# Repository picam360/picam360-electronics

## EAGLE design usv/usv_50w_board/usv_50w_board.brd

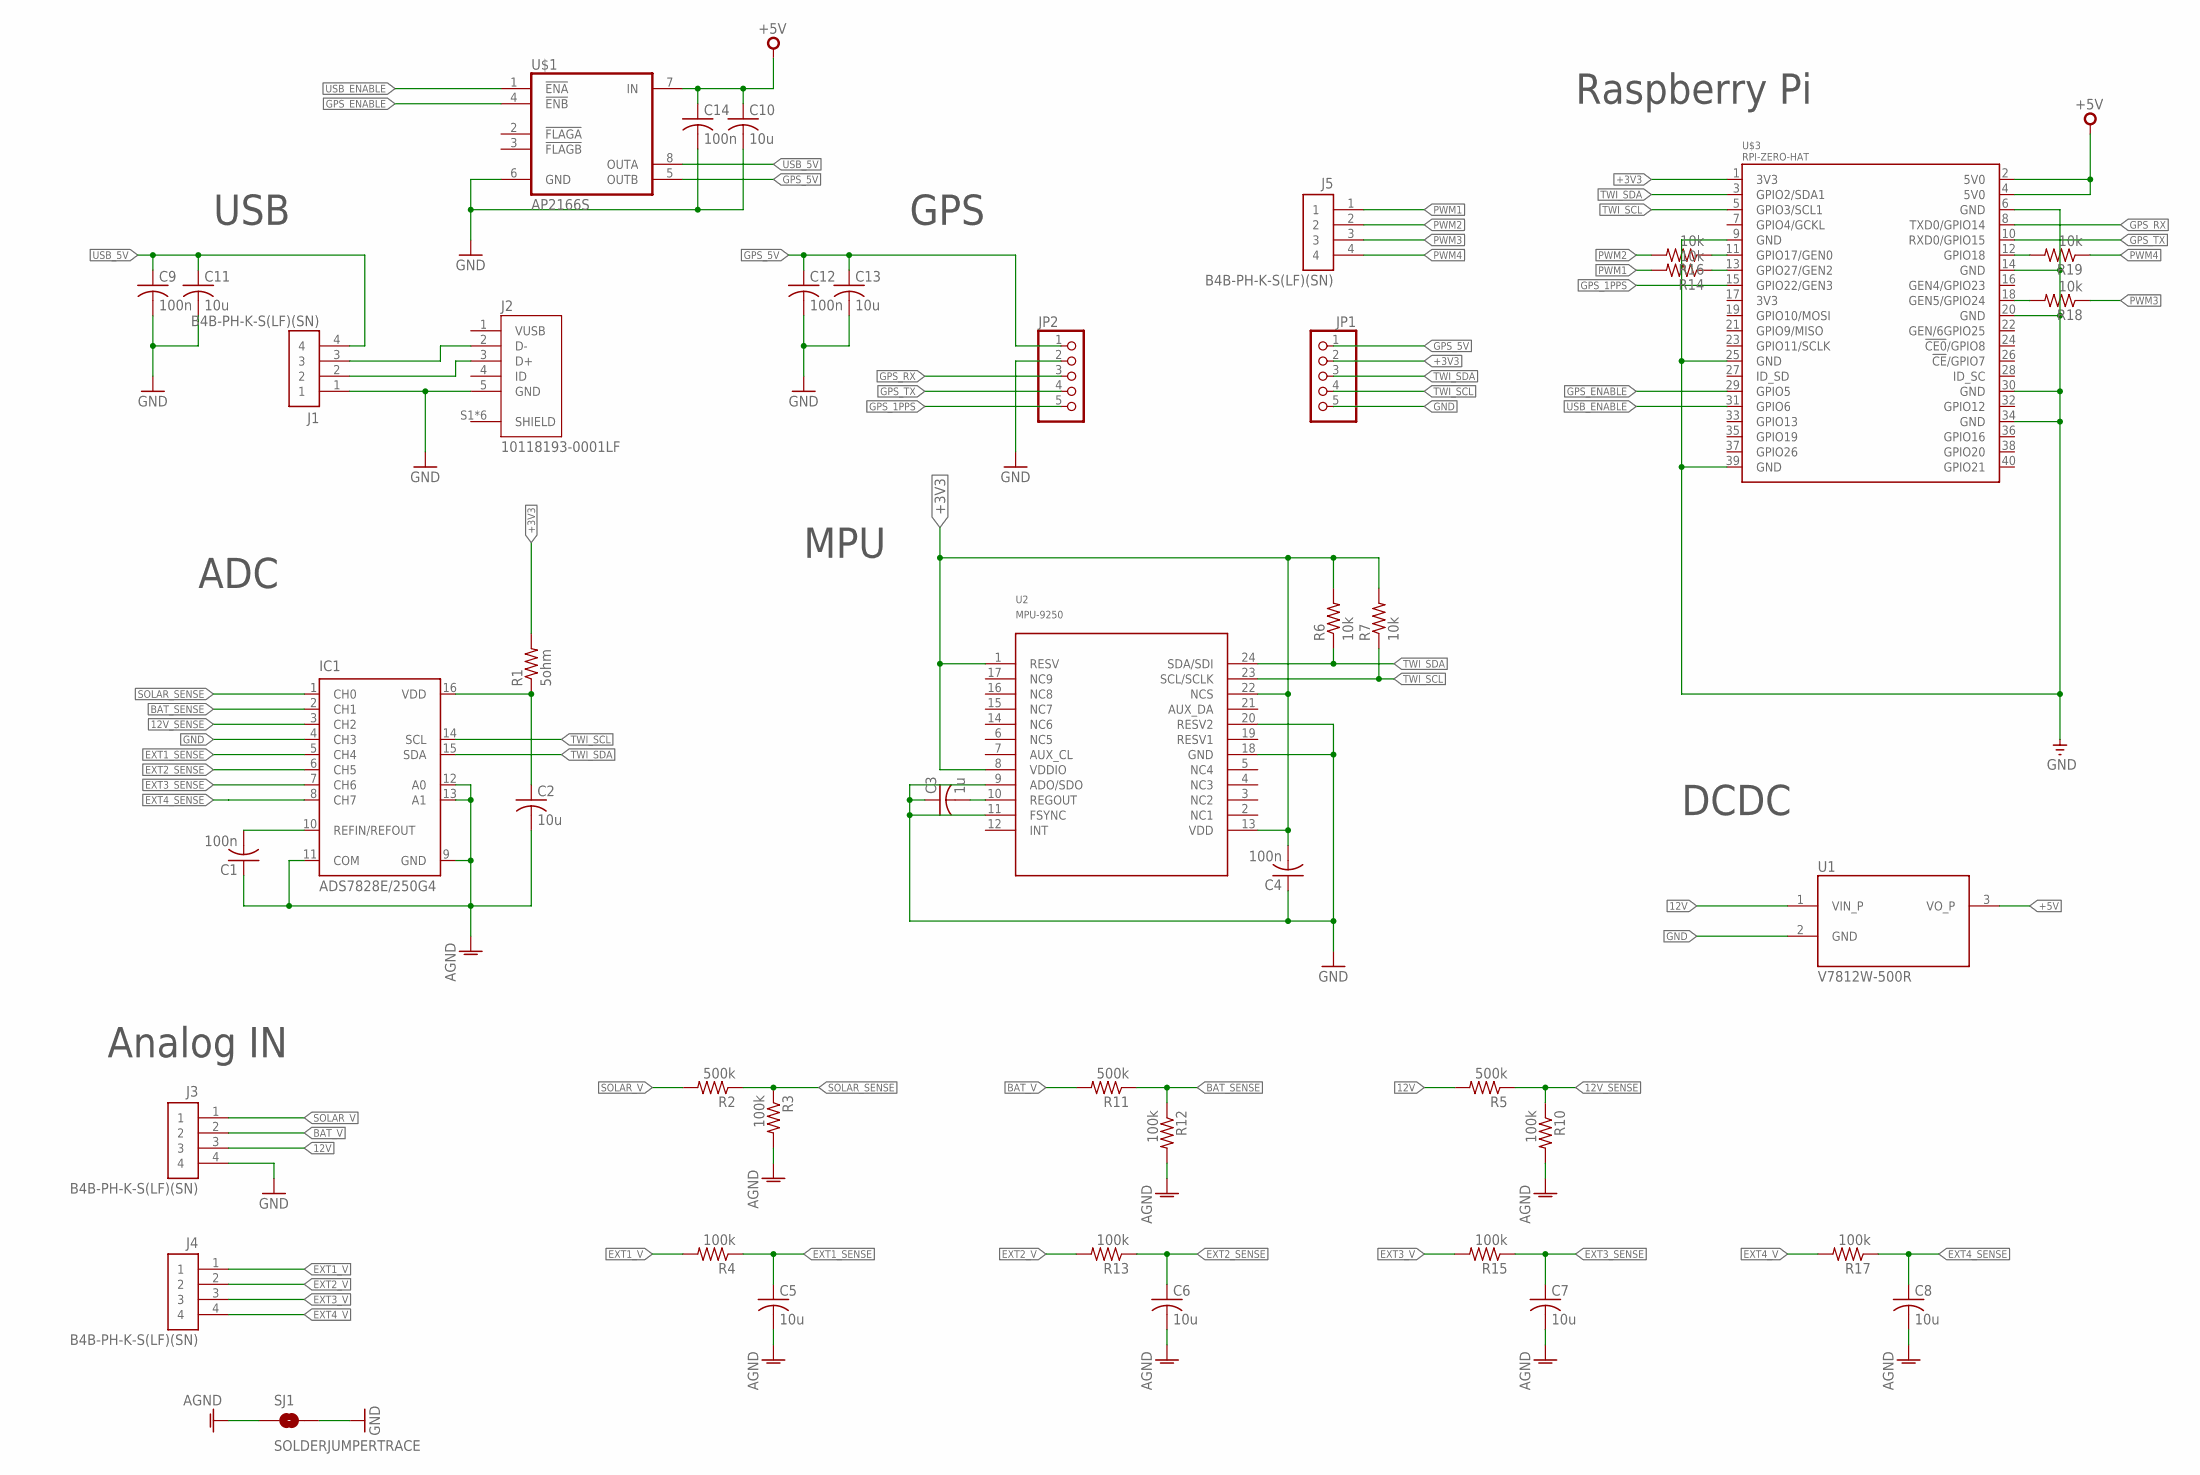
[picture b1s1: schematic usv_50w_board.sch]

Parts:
C1, C4, C9, C12, C14: 100n; C0603
C2, C5, C6, C7, C8, C10, C11, C13: 10u; C0603
C3: 1u; C0603
IC1: ADS7828E/250G4; TSSOP16-PW
J1, J3, J4, J5: B4B-PH-K-S(LF)(SN); JST_B4B-PH-K-S(LF)(SN)
J2: 10118193-0001LF; FCI_10118193-0001LF
JP1, JP2: PINHD-1X5; 1X05
R1: 5ohm; R0603
R2, R5, R11: 500k; R0603
R3, R4, R10, R12, R13, R15, R17: 100k; R0603
R6, R7, R14, R16, R18, R19: 10k; R0603
SJ1: SOLDERJUMPERTRACE; SJ_2S-TRACE
U1: V7812W-500R; CONV_V7812W-500R
U2: MPU-9250; LEAD-QFN24
U$1: AP2166S; SO08
U$3: RPI-ZERO-HAT; RASP_PI_ZERO_BOARD_FULL

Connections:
12V: J3.3, R5.2, U1.1 (VIN_P)
12V_SENSE: IC1.3 (CH2), R5.1, R10.1
+3V3: C4.2, JP1.2, R1.2, R6.2, R7.2, U2.1 (RESV), U2.8 (VDDIO), U2.13 (VDD), U2.22 (NCS), U$3.1 (3V3)
+5V: C10.1, C14.1, U1.3 (VO_P), U$1.7 (IN), U$3.2 (5V0), U$3.4 (5V0)
AGND: C1.1, C2.2, C5.2, C6.2, C7.2, C8.2, IC1.9 (GND), IC1.11 (COM), IC1.12 (A0), IC1.13 (A1), R3.2, R10.2, R12.2, SJ1.1
BAT_SENSE: IC1.2 (CH1), R11.1, R12.1
BAT_V: J3.2, R11.2
D_N: J1.3, J2.2 (D-)
D_P: J1.2, J2.3 (D+)
EXT1_SENSE: C5.1, IC1.5 (CH4), R4.1
EXT1_V: J4.1, R4.2
EXT2_SENSE: C6.1, IC1.6 (CH5), R13.1
EXT2_V: J4.2, R13.2
EXT3_SENSE: C7.1, IC1.7 (CH6), R15.1
EXT3_V: J4.3, R15.2
EXT4_SENSE: C8.1, IC1.8 (CH7), R17.1
EXT4_V: J4.4, R17.2
GND: C3.1, C4.1, C9.2, C10.2, C11.2, C12.2, C13.2, C14.2, IC1.4 (CH3), J1.1, J2.5 (GND), J3.4, JP1.5, JP2.2, SJ1.2, U1.2 (GND), U2.9 (ADO/SDO), U2.11 (FSYNC), U2.18 (GND), U2.20 (RESV2), U$1.6 (GND), U$3.6 (GND), U$3.9 (GND), U$3.14 (GND), U$3.20 (GND), U$3.25 (GND), U$3.30 (GND), U$3.34 (GND), U$3.39 (GND)
GPS_1PPS: JP2.5, U$3.15 (GPIO22/GEN3)
GPS_5V: C12.1, C13.1, JP1.1, JP2.1, U$1.5 (OUTB)
GPS_ENABLE: U$1.4 (!ENB!), U$3.29 (GPIO5)
GPS_RX: JP2.3, U$3.8 (TXD0/GPIO14)
GPS_TX: JP2.4, U$3.10 (RXD0/GPIO15)
unnamed: R14.1, U$3.13 (GPIO27/GEN2)
unnamed: C3.2, U2.10 (REGOUT)
unnamed: R16.1, U$3.11 (GPIO17/GEN0)
unnamed: R18.2, U$3.18 (GEN5/GPIO24)
unnamed: R19.2, U$3.12 (GPIO18)
unnamed: C2.1, IC1.16 (VDD), R1.1
unnamed: C1.2, IC1.10 (REFIN/REFOUT)
PWM1: J5.1, R14.2
PWM2: J5.2, R16.2
PWM3: J5.3, R18.1
PWM4: J5.4, R19.1
SOLAR_SENSE: IC1.1 (CH0), R2.1, R3.1
SOLAR_V: J3.1, R2.2
TWI_SCL: IC1.14 (SCL), JP1.4, R7.1, U2.23 (SCL/SCLK), U$3.5 (GPIO3/SCL1)
TWI_SDA: IC1.15 (SDA), JP1.3, R6.1, U2.24 (SDA/SDI), U$3.3 (GPIO2/SDA1)
USB_5V: C9.1, C11.1, J1.4, U$1.8 (OUTA)
USB_ENABLE: U$1.1 (!ENA!), U$3.31 (GPIO6)

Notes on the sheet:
USB
Raspberry Pi
GPS
ADC
MPU
Analog IN
DCDC

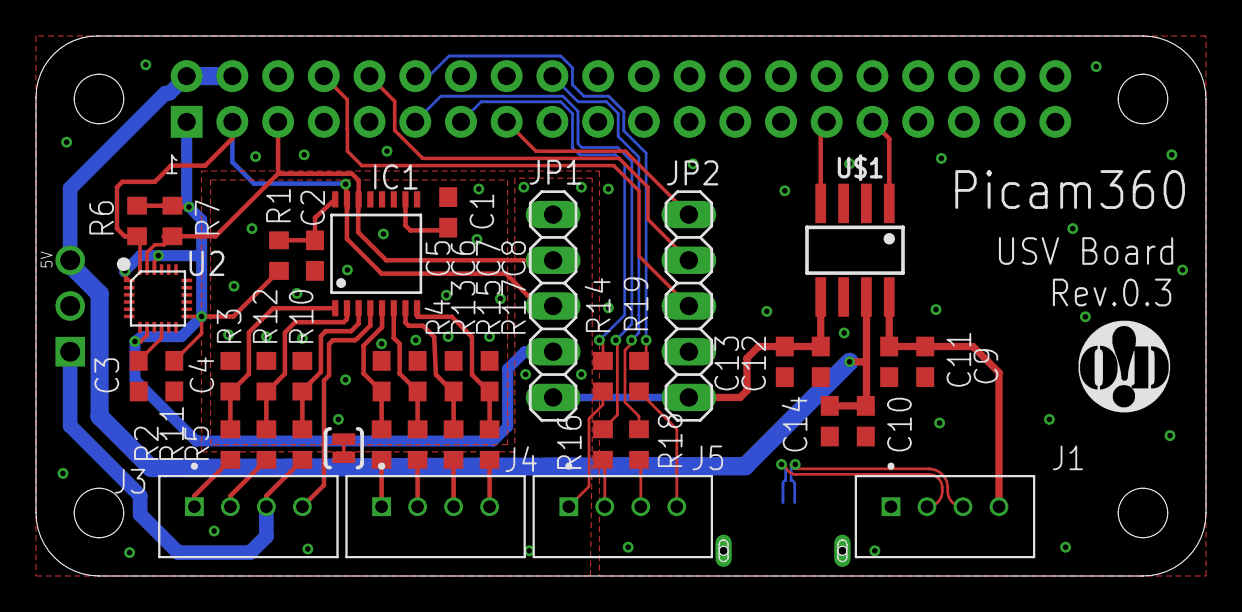
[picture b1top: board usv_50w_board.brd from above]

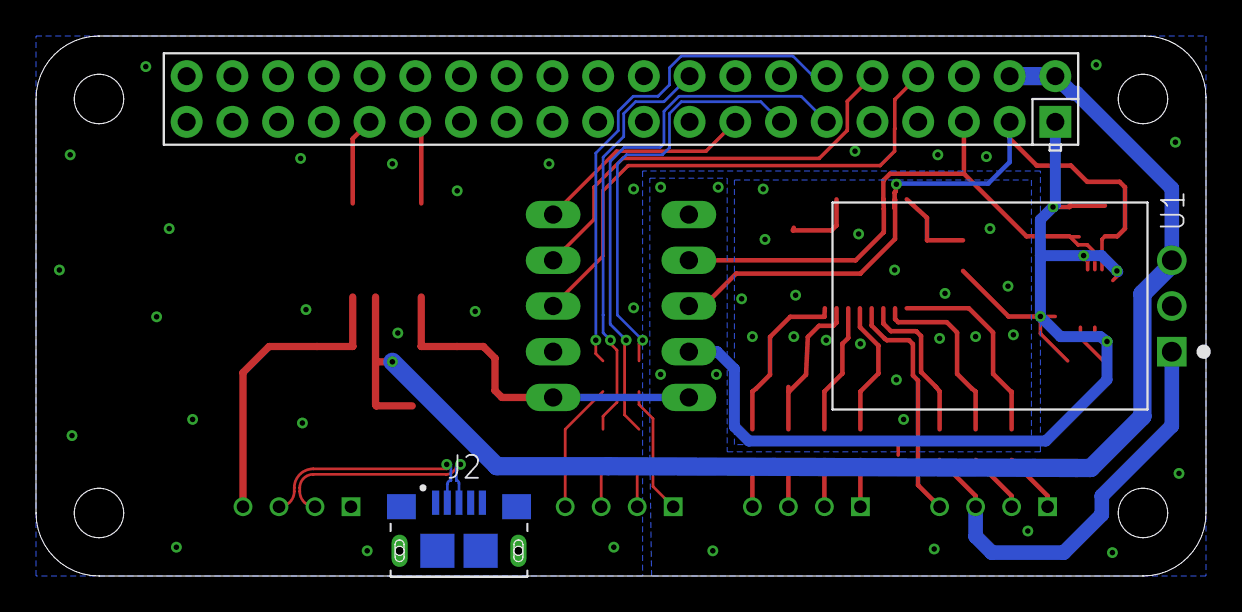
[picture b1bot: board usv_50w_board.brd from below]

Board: 2 copper layers, 65.0 x 30.0 mm, 45 parts (2 on the bottom side), 40 nets.

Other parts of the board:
LOGO1: OHMYDIGIFAB_LOGO

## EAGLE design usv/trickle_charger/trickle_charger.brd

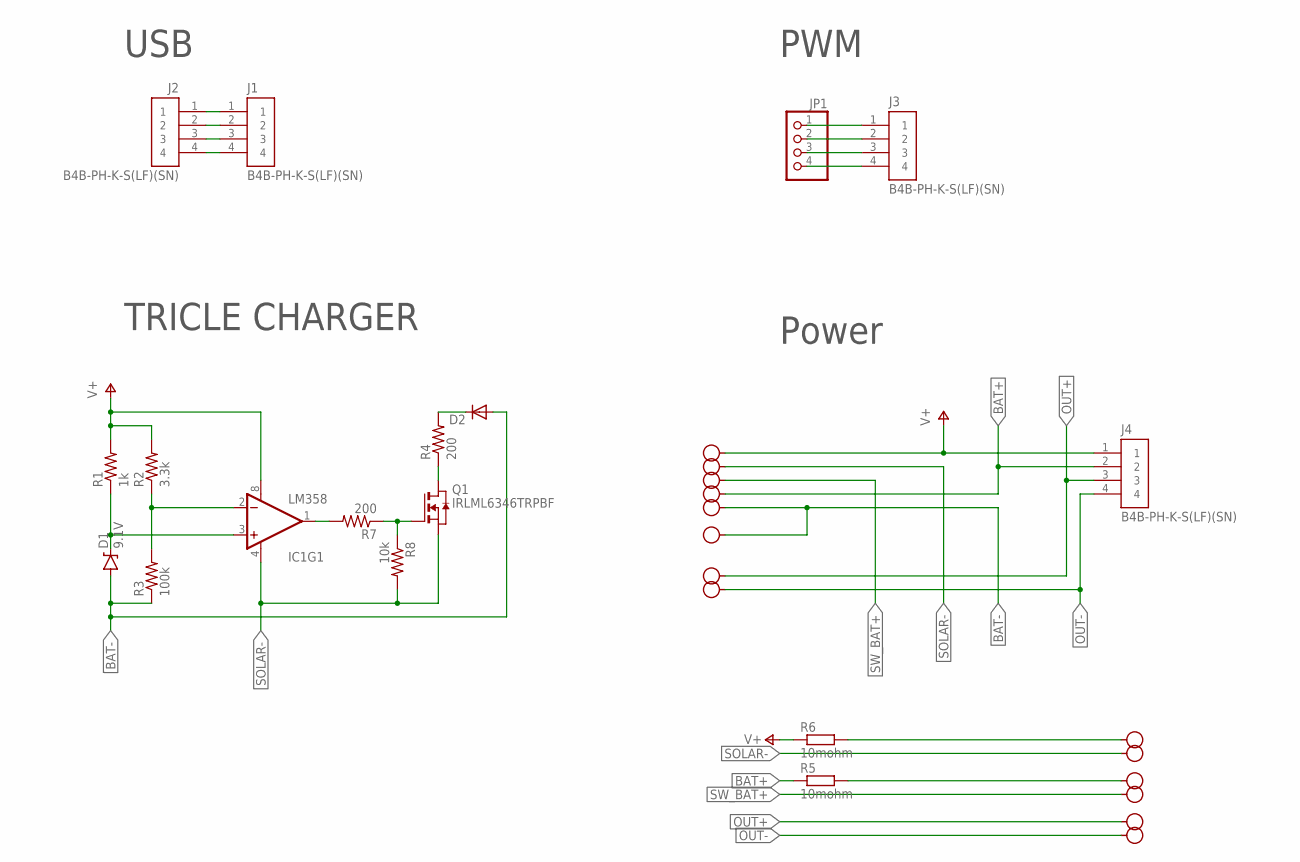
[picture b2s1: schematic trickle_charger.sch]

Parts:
D1: 9.1V; DIODE-ZENER
D2: DIODE-D-7.5; D-7.5
H1, H2, H3, H4, H5, H6, H7, H8, H9, H10, H11, H12, H13, H14: SEW_HOLE-SMALL; SIMPLE_HOLE_SM
IC1: LM358; DIP08
J1, J2, J3, J4: B4B-PH-K-S(LF)(SN); JST_B4B-PH-K-S(LF)(SN)
JP1: PINHD-1X4/90; 1X04/90
Q1: IRLML6346TRPBF; SOT23
R1: 1k; R0603
R2: 3.3k; R0603
R3: 100k; R0603
R4, R7: 200; R0603
R5, R6: 10mohm; R2512
R8: 10k; R0603

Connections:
BAT+: H3.P$1, J4.2, R5.1
BAT-: D1.P$2 (A), D2.A, H4.P$1, H5.P$1, R3.1
unnamed: D1.P$1 (C), IC1.3 (+IN), R1.1
unnamed: D2.C, R4.2
unnamed: IC1.2 (-IN), R2.1, R3.2
unnamed: Q1.3 (D), R4.1
unnamed: IC1.1 (OUT), R7.2
unnamed: Q1.1 (G), R7.1, R8.1
unnamed: J3.1, JP1.1
unnamed: J3.2, JP1.2
unnamed: J3.3, JP1.3
unnamed: J3.4, JP1.4
unnamed: H9.P$1, R6.2
unnamed: H11.P$1, R5.2
OUT+: H7.P$1, H13.P$1, J4.3
OUT-: H8.P$1, H14.P$1, J4.4
SOLAR+: R6.1
SOLAR-: H2.P$1, H10.P$1, IC1.4 (V-), Q1.2 (S), R8.2
SW_BAT+: H6.P$1, H12.P$1
USB_D_N: J1.3, J2.3
USB_D_P: J1.2, J2.2
USB_GND: J1.1, J2.1
USB_PWR: J1.4, J2.4
V+: H1.P$1, IC1.8 (V+), J4.1, R1.2, R2.2

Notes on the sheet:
USB
PWM
Power
TRICLE CHARGER

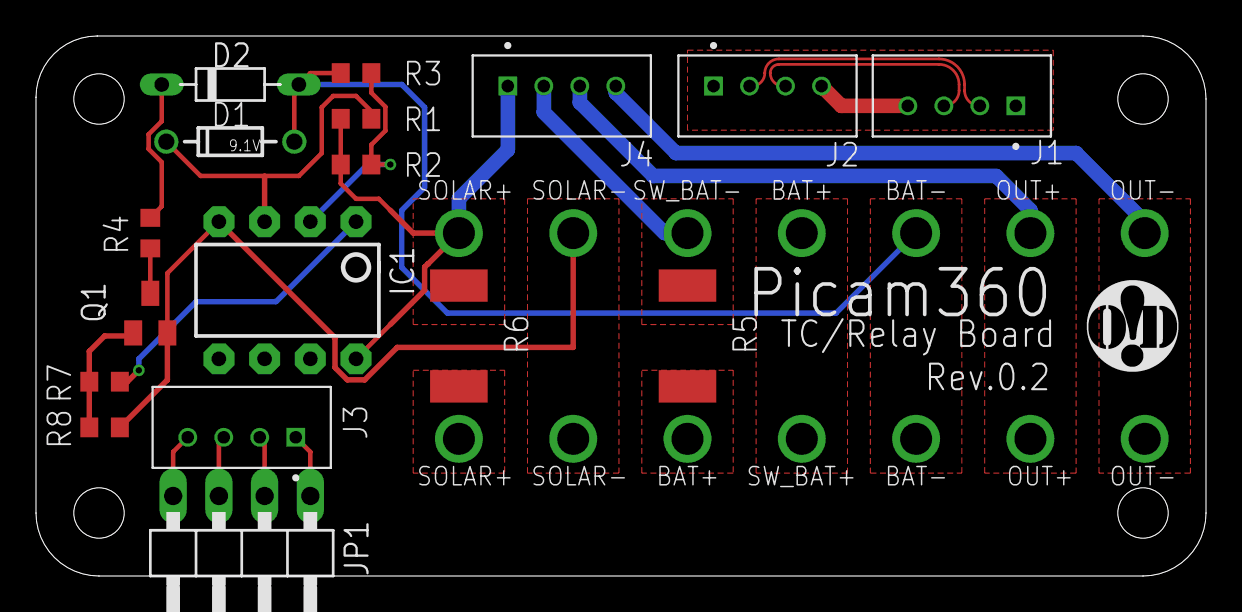
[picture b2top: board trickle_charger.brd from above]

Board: 2 copper layers, 65.0 x 30.0 mm, 32 parts (0 on the bottom side), 23 nets.

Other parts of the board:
LOGO1: OHMYDIGIFAB_LOGO

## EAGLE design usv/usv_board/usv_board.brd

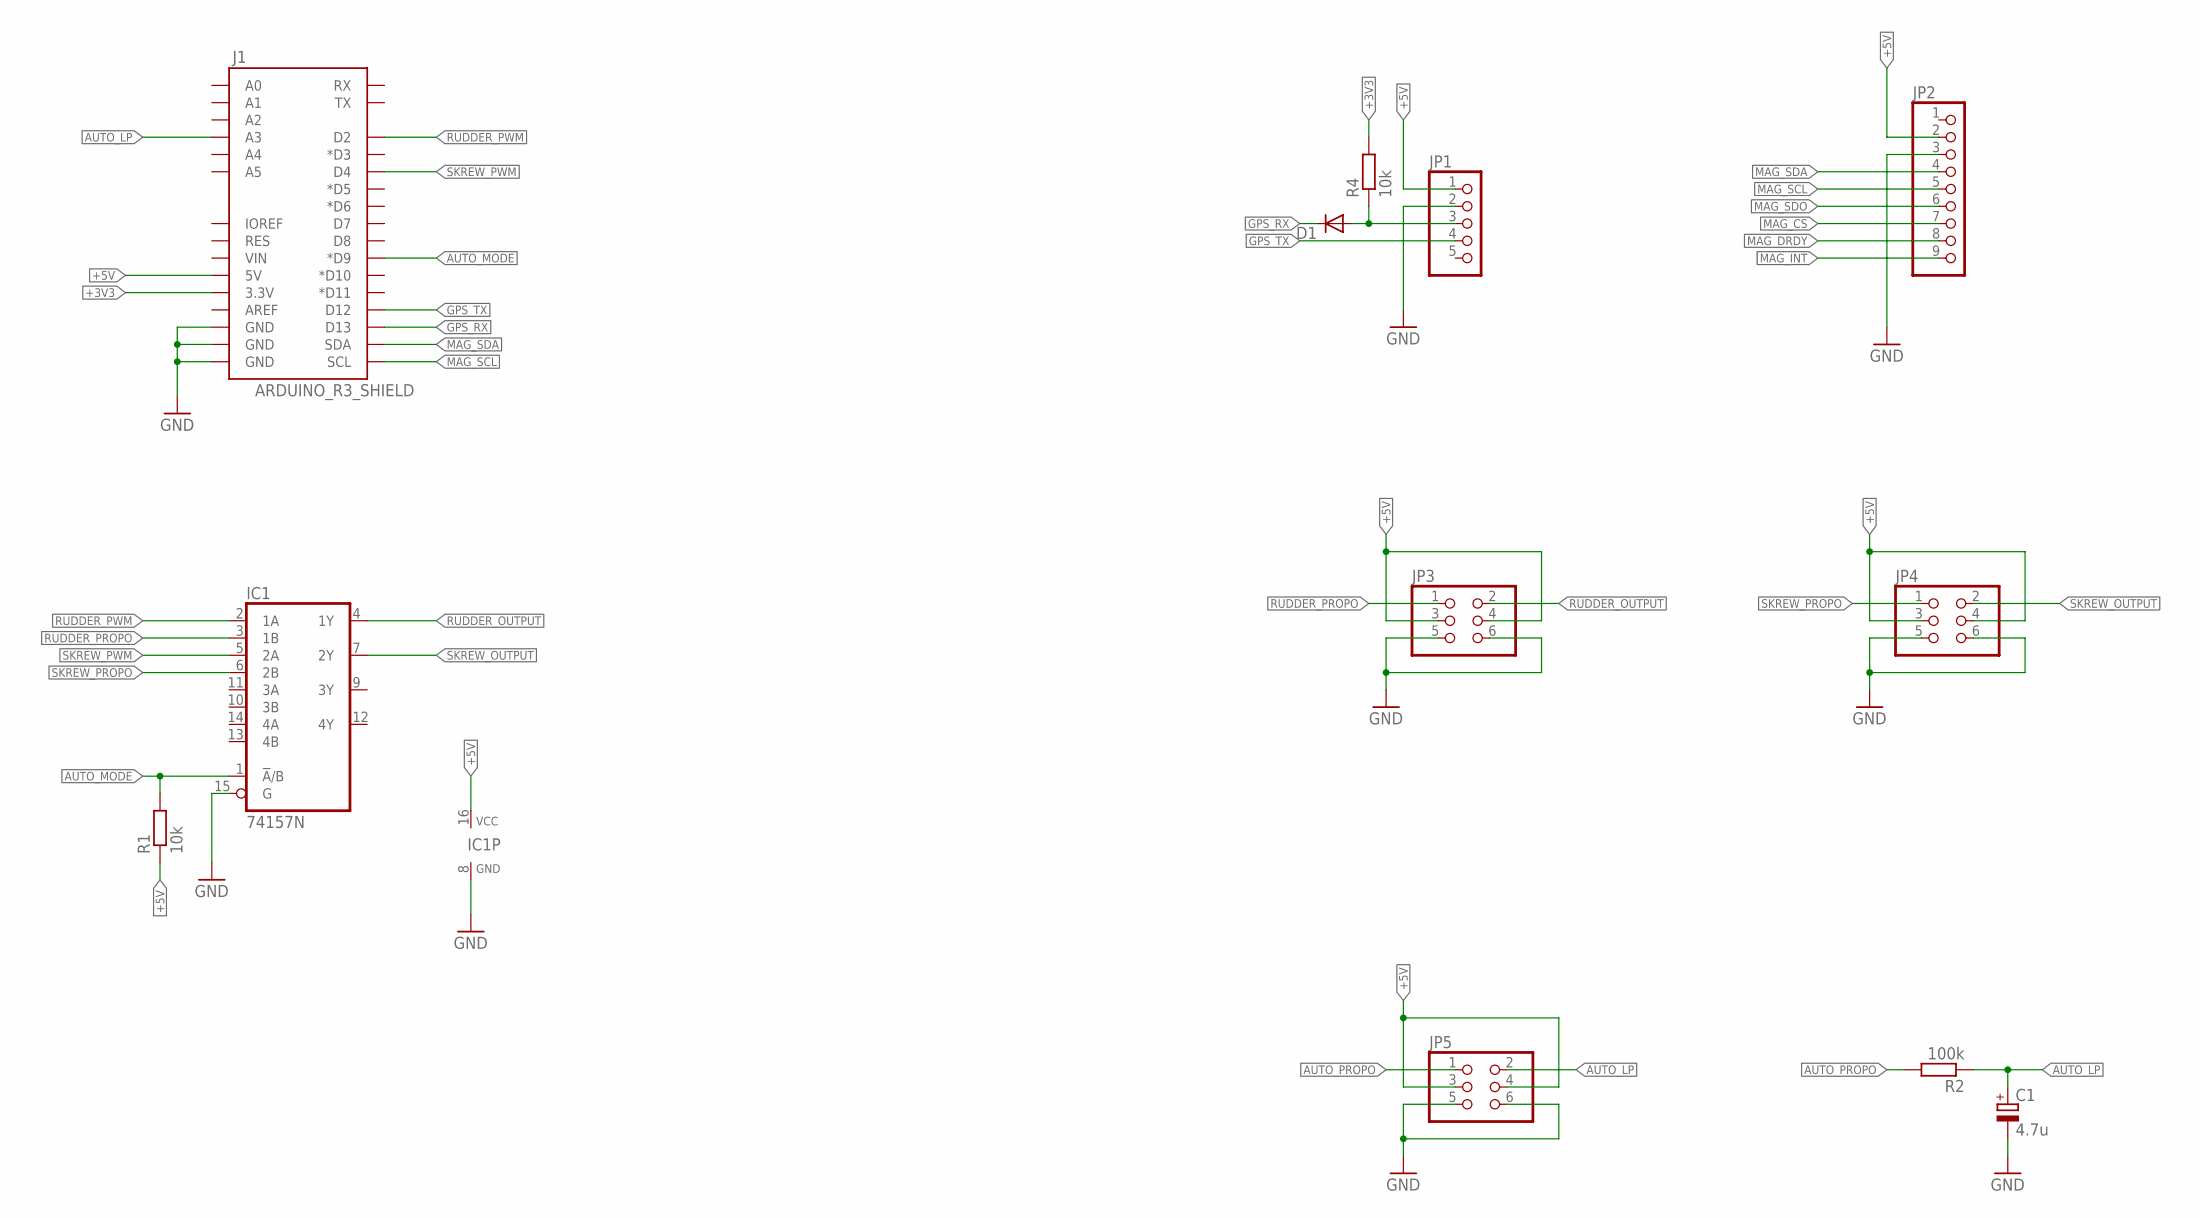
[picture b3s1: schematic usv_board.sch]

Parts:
C1: 4.7u; E2-4
D1: DIODE-D-7.5; D-7.5
IC1: 74157N; DIL16
J1: ARDUINO_R3_SHIELD; UNO_R3_SHIELD
JP1: PINHD-1X5; 1X05
JP2: PINHD-1X9; 1X09
JP3, JP4, JP5: PINHD-2X3; 2X03
R1, R4: 10k; 0207/7
R2: 100k; 0207/7

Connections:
+3V3: J1.3.3V, R4.2
+5V: IC1.16 (VCC), J1.5V, JP1.1, JP2.2, JP3.3, JP3.4, JP4.3, JP4.4, JP5.3, JP5.4, R1.1
AUTO_LP: C1.+, J1.A3, JP5.2, R2.1
AUTO_MODE: IC1.1 (!A!/B), J1.D9 (*D9), R1.2
AUTO_PROPO: JP5.1, R2.2
GND: C1.-, IC1.8 (GND), IC1.15 (G), J1.GND@0 (GND), J1.GND@1 (GND), J1.GND@2 (GND), JP1.2, JP2.3, JP3.5, JP3.6, JP4.5, JP4.6, JP5.5, JP5.6
GPS_RX: D1.C, J1.D13
GPS_TX: J1.D12, JP1.4
MAG_CS: JP2.7
MAG_DRDY: JP2.8
MAG_INT: JP2.9
MAG_SCL: J1.SCL, JP2.5
MAG_SDA: J1.SDA, JP2.4
MAG_SDO: JP2.6
unnamed: D1.A, JP1.3, R4.1
RUDDER_OUTPUT: IC1.4 (1Y), JP3.2
RUDDER_PROPO: IC1.3 (1B), JP3.1
RUDDER_PWM: IC1.2 (1A), J1.D2
SKREW_OUTPUT: IC1.7 (2Y), JP4.2
SKREW_PROPO: IC1.6 (2B), JP4.1
SKREW_PWM: IC1.5 (2A), J1.D4

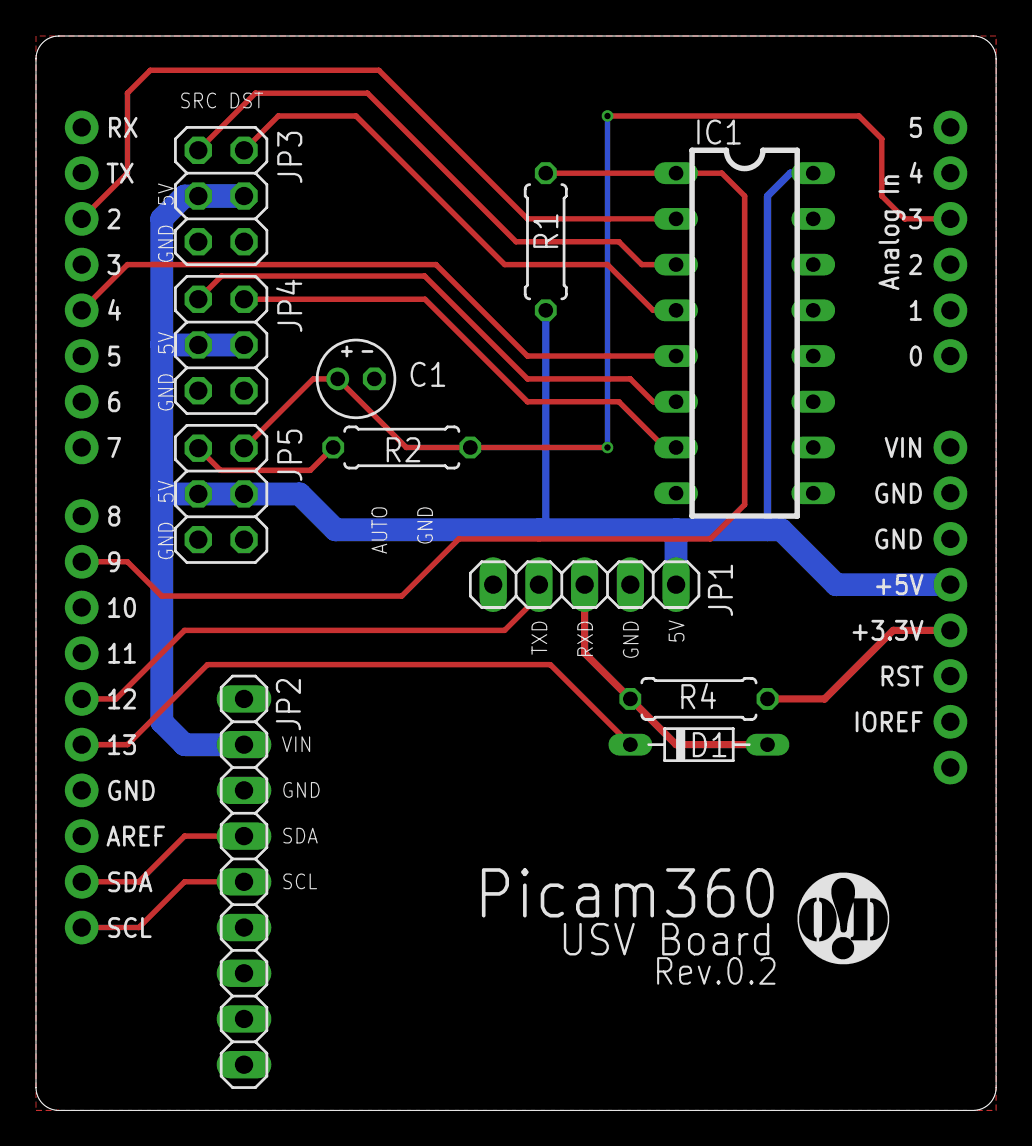
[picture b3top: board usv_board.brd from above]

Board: 2 copper layers, 53.3 x 59.7 mm, 13 parts (0 on the bottom side), 17 nets.

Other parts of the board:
LOGO1: OHMYDIGIFAB_LOGO

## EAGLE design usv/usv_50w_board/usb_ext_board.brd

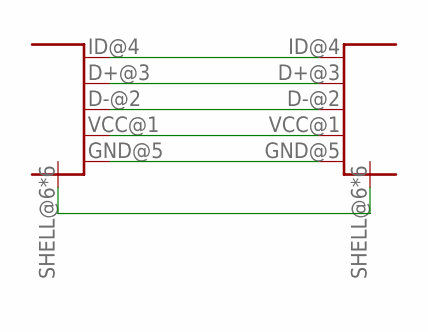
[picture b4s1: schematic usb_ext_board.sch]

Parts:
MALE1, MALE2: USB-ID; USB3150-30-130

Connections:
D+: MALE1.D+@3 (D+), MALE2.D+@3 (D+)
D-: MALE1.D-@2 (D-), MALE2.D-@2 (D-)
GND: MALE1.GND@5 (GND), MALE1.SHELL@6 (SHELL), MALE1.SHELL@7 (SHELL), MALE1.SHELL@8 (SHELL), MALE1.SHELL@9 (SHELL), MALE1.SHELL@10 (SHELL), MALE1.SHELL@11 (SHELL), MALE2.GND@5 (GND), MALE2.SHELL@6 (SHELL), MALE2.SHELL@7 (SHELL), MALE2.SHELL@8 (SHELL), MALE2.SHELL@9 (SHELL), MALE2.SHELL@10 (SHELL), MALE2.SHELL@11 (SHELL)
ID: MALE1.ID@4 (ID), MALE2.ID@4 (ID)
VCC: MALE1.VCC@1 (VBUS), MALE2.VCC@1 (VBUS)

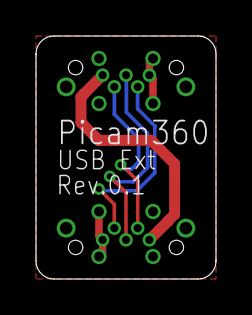
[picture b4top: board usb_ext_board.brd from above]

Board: 2 copper layers, 10.0 x 13.5 mm, 3 parts (1 on the bottom side), 5 nets.

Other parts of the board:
LOGO1: OHMYDIGIFAB_LOGO

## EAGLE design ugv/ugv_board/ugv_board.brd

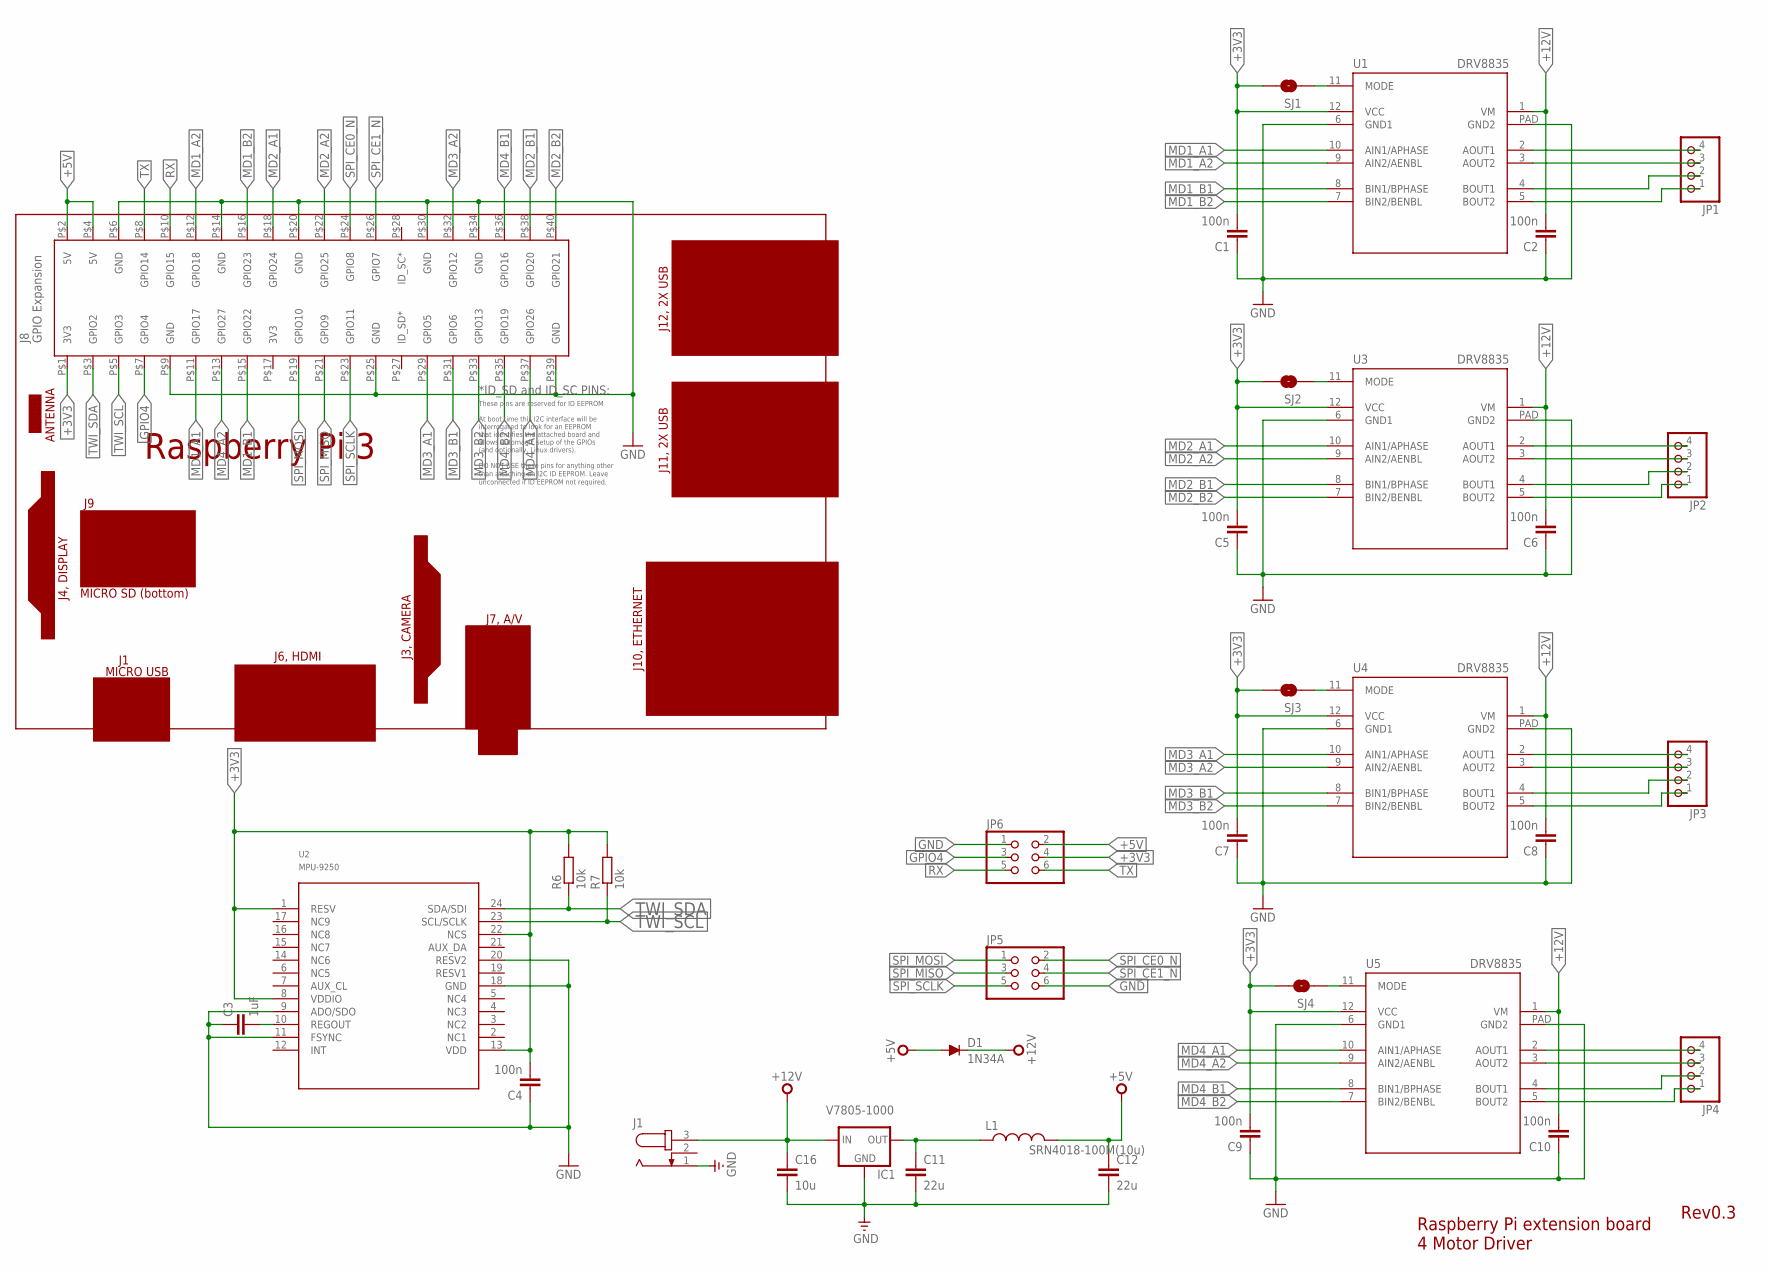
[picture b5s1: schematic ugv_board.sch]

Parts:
C1, C2, C4, C5, C6, C7, C8, C9, C10: 100n; C0402
C3: 1uF; C0402
C11, C12: 22u; C0603
C16: 10u; C0603
D1: 1N34A; DO07
IC1: V7805-1000; DIP_3PIN
J1: JACK-PLUG0; SPC4077
JP1, JP2, JP3, JP4: PINHD-1X4M; 1X04M
JP5, JP6: PINHD-2X3; 2X03
L1: SRN4018-100M(10u); BOURNS-SRN4018
PCB1: RPI3
R6, R7: 10k; R0402
SJ1, SJ2, SJ3, SJ4: SOLDERJUMPERNC; SJ_2S
U1, U3, U4, U5: DRV8835; WSON_2X3
U2: MPU-9250; LEAD-QFN24

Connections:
+3V3: C1.2, C4.2, C5.2, C7.2, C9.2, JP6.4, PCB1.P$1 (3V3), R6.2, R7.2, SJ1.2, SJ2.2, SJ3.2, SJ4.2, U1.12 (VCC), U2.1 (RESV), U2.8 (VDDIO), U2.13 (VDD), U2.22 (NCS), U3.12 (VCC), U4.12 (VCC), U5.12 (VCC)
+5V: C12.1, D1.A, JP6.2, L1.P$1 (1), PCB1.P$2 (5V), PCB1.P$4 (5V)
+12V: C2.2, C6.2, C8.2, C10.2, C16.1, D1.C, IC1.IN, J1.3, U1.1 (VM), U3.1 (VM), U4.1 (VM), U5.1 (VM)
GND: C1.1, C2.1, C3.1, C4.1, C5.1, C6.1, C7.1, C8.1, C9.1, C10.1, C11.2, C12.2, C16.2, IC1.GND, J1.1, JP5.6, JP6.1, PCB1.P$6 (GND), PCB1.P$9 (GND), PCB1.P$14 (GND), PCB1.P$20 (GND), PCB1.P$25 (GND), PCB1.P$30 (GND), PCB1.P$34 (GND), PCB1.P$39 (GND), U1.6 (GND1), U1.PAD (GND2), U2.9 (ADO/SDO), U2.11 (FSYNC), U2.18 (GND), U2.20 (RESV2), U3.6 (GND1), U3.PAD (GND2), U4.6 (GND1), U4.PAD (GND2), U5.6 (GND1), U5.PAD (GND2)
GPIO4: JP6.3, PCB1.P$7 (GPIO4)
MD1_A1: PCB1.P$11 (GPIO17), U1.10 (AIN1/APHASE)
MD1_A2: PCB1.P$12 (GPIO18), U1.9 (AIN2/AENBL)
MD1_B1: PCB1.P$15 (GPIO22), U1.8 (BIN1/BPHASE)
MD1_B2: PCB1.P$16 (GPIO23), U1.7 (BIN2/BENBL)
MD2_A1: PCB1.P$18 (GPIO24), U3.10 (AIN1/APHASE)
MD2_A2: PCB1.P$22 (GPIO25), U3.9 (AIN2/AENBL)
MD2_B1: PCB1.P$38 (GPIO20), U3.8 (BIN1/BPHASE)
MD2_B2: PCB1.P$40 (GPIO21), U3.7 (BIN2/BENBL)
MD3_A1: PCB1.P$29 (GPIO5), U4.10 (AIN1/APHASE)
MD3_A2: PCB1.P$32 (GPIO12), U4.9 (AIN2/AENBL)
MD3_B1: PCB1.P$31 (GPIO6), U4.8 (BIN1/BPHASE)
MD3_B2: PCB1.P$33 (GPIO13), U4.7 (BIN2/BENBL)
MD4_A1: PCB1.P$37 (GPIO26), U5.10 (AIN1/APHASE)
MD4_A2: PCB1.P$13 (GPIO27), U5.9 (AIN2/AENBL)
MD4_B1: PCB1.P$36 (GPIO16), U5.8 (BIN1/BPHASE)
MD4_B2: PCB1.P$35 (GPIO19), U5.7 (BIN2/BENBL)
unnamed: JP1.4, U1.2 (AOUT1)
unnamed: JP1.3, U1.3 (AOUT2)
unnamed: JP1.2, U1.4 (BOUT1)
unnamed: JP4.4, U5.2 (AOUT1)
unnamed: JP1.1, U1.5 (BOUT2)
unnamed: JP2.4, U3.2 (AOUT1)
unnamed: JP2.3, U3.3 (AOUT2)
unnamed: JP2.2, U3.4 (BOUT1)
unnamed: JP2.1, U3.5 (BOUT2)
unnamed: JP3.4, U4.2 (AOUT1)
unnamed: JP3.3, U4.3 (AOUT2)
unnamed: JP3.2, U4.4 (BOUT1)
unnamed: JP3.1, U4.5 (BOUT2)
unnamed: JP4.3, U5.3 (AOUT2)
unnamed: JP4.2, U5.4 (BOUT1)
unnamed: JP4.1, U5.5 (BOUT2)
unnamed: SJ4.1, U5.11 (MODE)
unnamed: SJ3.1, U4.11 (MODE)
unnamed: SJ2.1, U3.11 (MODE)
unnamed: SJ1.1, U1.11 (MODE)
unnamed: C11.1, IC1.OUT, L1.P$2 (2)
REGOUT: C3.2, U2.10 (REGOUT)
RX: JP6.5, PCB1.P$10 (GPIO15)
SPI_CE0_N: JP5.2, PCB1.P$24 (GPIO8)
SPI_CE1_N: JP5.4, PCB1.P$26 (GPIO7)
SPI_MISO: JP5.3, PCB1.P$21 (GPIO9)
SPI_MOSI: JP5.1, PCB1.P$19 (GPIO10)
SPI_SCLK: JP5.5, PCB1.P$23 (GPIO11)
TWI_SCL: PCB1.P$5 (GPIO3), R7.1, U2.23 (SCL/SCLK)
TWI_SDA: PCB1.P$3 (GPIO2), R6.1, U2.24 (SDA/SDI)
TX: JP6.6, PCB1.P$8 (GPIO14)

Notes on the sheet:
Rev0.3
Raspberry Pi extension board 4 Motor Driver

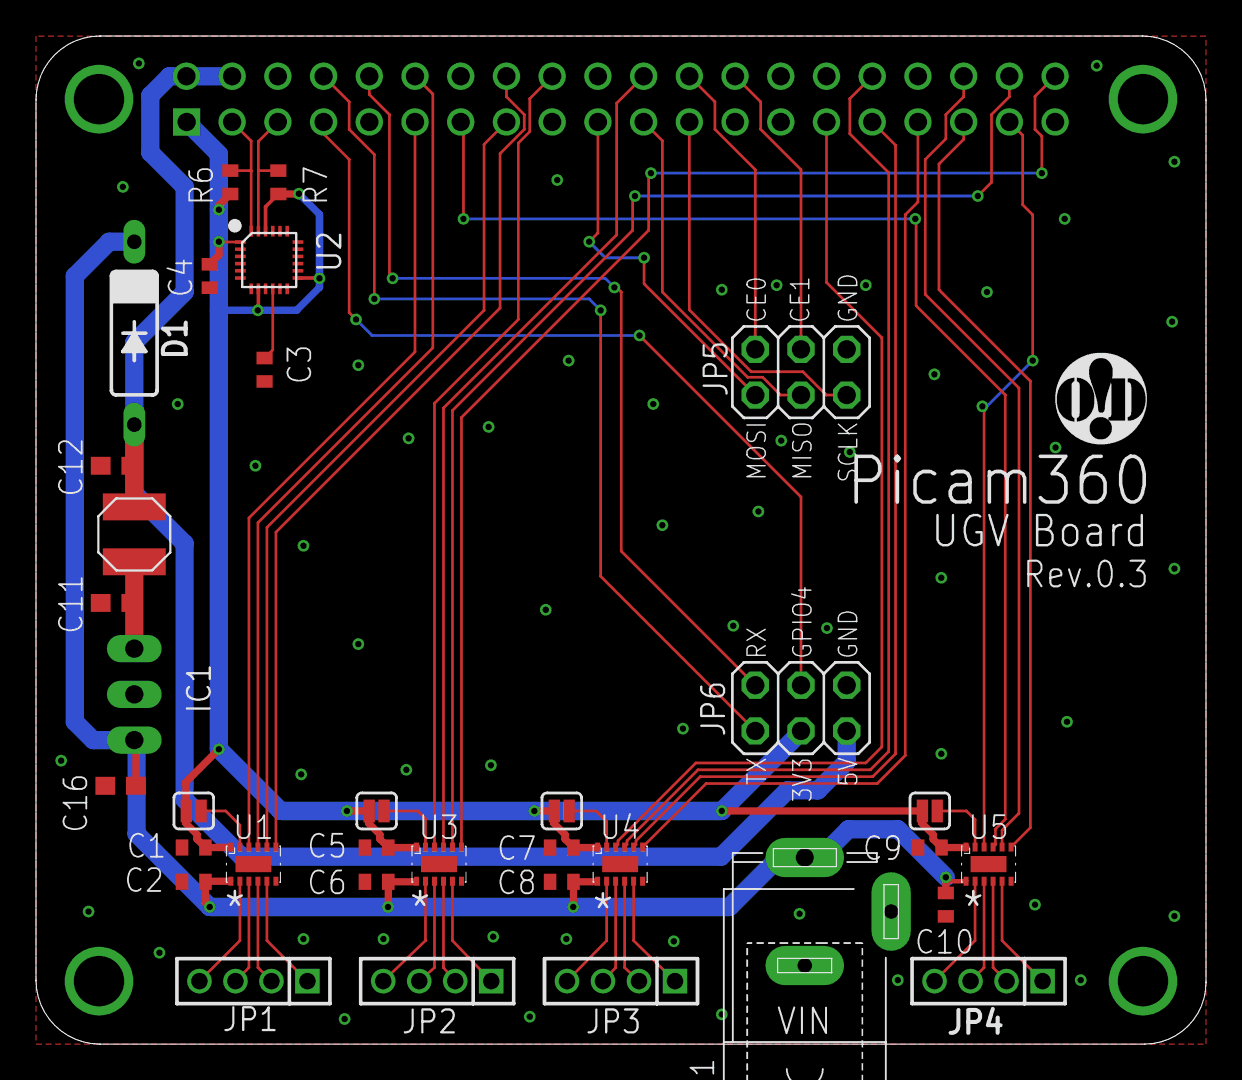
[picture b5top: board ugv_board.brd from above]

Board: 2 copper layers, 65.0 x 56.0 mm, 36 parts (0 on the bottom side), 52 nets.

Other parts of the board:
U$1: OHMYDIGIFAB_LOGO

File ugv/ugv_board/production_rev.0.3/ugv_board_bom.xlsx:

BOM Example
Elecrow PN | Parts | Value | Package | QTY | Digikey/Mouser/Manufacturer Part | Remark/ Link
 | J1 |  |  | 1 | DO NOT Solder this parts
 | JP1, JP2, JP3, JP4 |  |  | 4 | DO NOT Solder this parts
 | JP5, JP6 |  |  | 2 | DO NOT Solder this parts
 | C1, C2, C4, C5, C6, C7, C8, C9, C10 | 100n | C0402 | 9 | GRM155R61H104KE19D/490-11917-1-ND | https://www.digikey.jp/product-detail/ja/murata-electronics-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
 | R6, R7 | 10k | R0402 | 2 | ERJ-2GEJ103X/P10KJCT-ND | https://www.digikey.jp/product-detail/ja/panasonic-electroni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
 | C16 | 10u | C0603 | 1 | GRM188R61E106MA73D/490-7202-1-ND | https://www.digikey.jp/product-detail/ja/murata-electronics-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
 | D1 | 1N34A |  | 1 | DO NOT Solder this parts
 | C3 | 1uF | C0402 | 1 | GCM155C71A105KE38D/490-13409-1-ND | https://www.digikey.jp/product-detail/ja/murata-electronics-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
 | C11, C12 | 22u | C0603 | 2 | GRM188R6YA106MA73D/490-13248-1-ND | https://www.digikey.jp/product-detail/ja/murata-electronics-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
 | U1, U3, U4, U5 | DRV8835 | WSON_2X3 | 4 | DRV8835DSSR/296-30391-1-ND/3188673 | https://www.digikey.jp/product-detail/ja/texas-instruments/D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
 | U2 | MPU-9250 |  | 1 | DO NOT Solder this parts
 | PCB1 | RPI3 |  | 1 | DO NOT Solder this parts
 | SJ1, SJ2, SJ3, SJ4 | SOLDERJUMPERNC |  | 4 | DO NOT Solder this parts
 | L1 | SRN4018-100M(10u) | BOURNS-SRN4018 | 1 | SRN4018-100M/SRN4018-100MCT-ND | https://www.digikey.jp/product-detail/ja/bourns-inc/SRN4018-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
 | IC1 | V7805-1000 |  | 1 | DO NOT Solder this parts

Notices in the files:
parts and their libraries:
SparkFun-Aesthetics: Licensing: Creative Commons ShareAlike 4.0 International - https://creativecommons.org/licenses/by-sa/4.0
dports: Copyright (C) 2008, Bob Starr
supply0: Copyright (C) 2007, Bob Starr
